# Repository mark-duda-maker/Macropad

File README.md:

## The Case

## The PCB

## The Schematic

## The Bom
4x M3x16mm screws
4x M3x5mx4mm heatset inserts
9x Blank DSA keycaps
9x MX-Style switches
9x Through-hole 1N4148 Diodes
1x 0.91" 128x32 OLED Display
1x EC11 Rotary Encoder
1x XIAO RP2040

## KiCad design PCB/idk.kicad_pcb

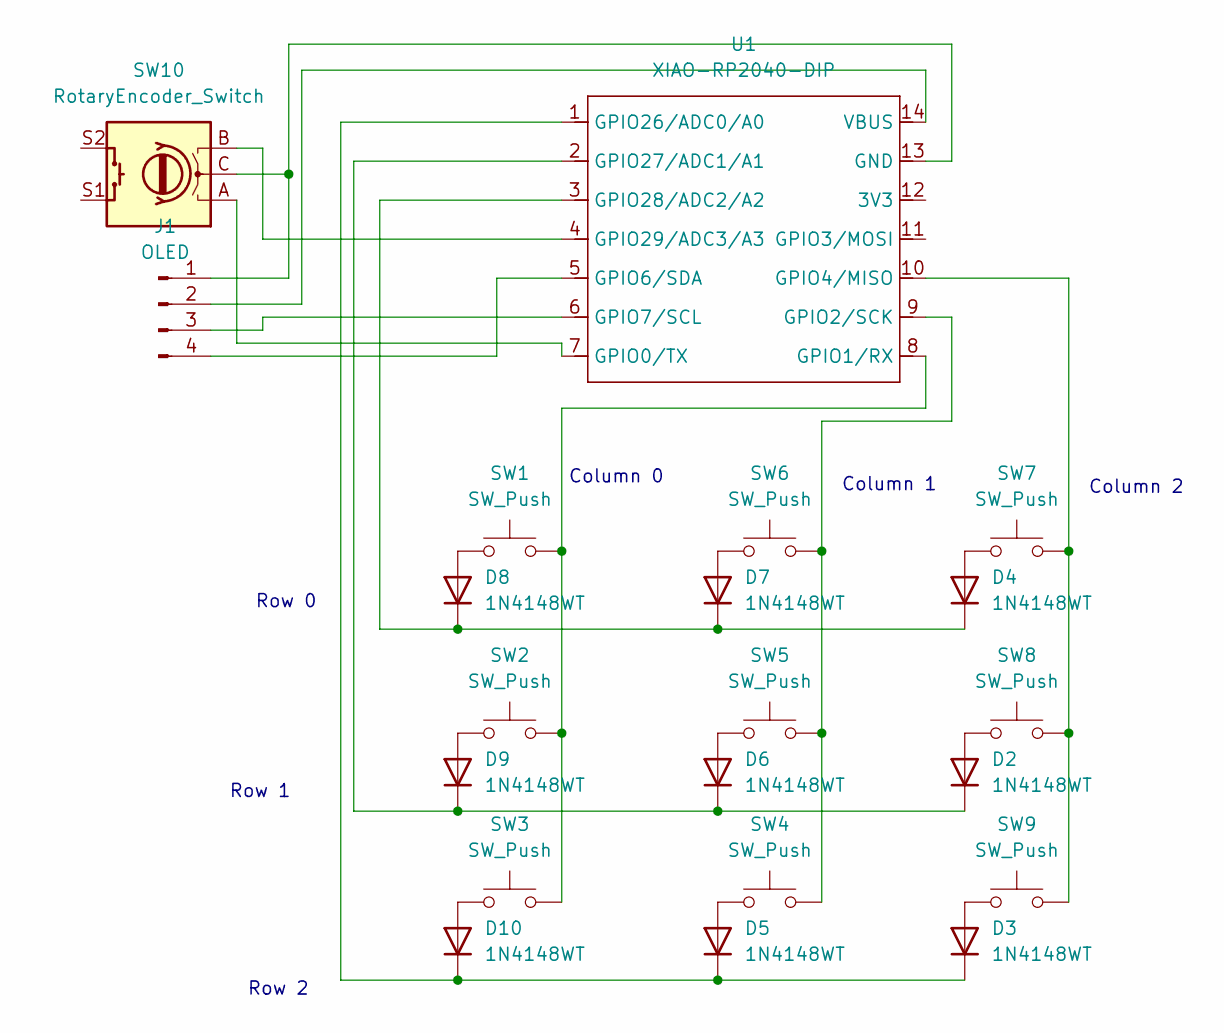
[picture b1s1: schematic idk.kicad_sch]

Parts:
D2, D3, D4, D5, D6, D7, D8, D9, D10: 1N4148WT; D_DO-35_SOD27_P7.62mm_Horizontal
J1: OLED; SSD1306-0.91-OLED-4pin-128x32
SW1, SW2, SW3, SW4, SW5, SW6, SW7, SW8, SW9: SW_Push; SW_Cherry_MX_1.00u_PCB
SW10: RotaryEncoder_Switch; RotaryEncoder_Alps_EC11E-Switch_Vertical_H20mm_CircularMoun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
U1: XIAO-RP2040-DIP

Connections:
unnamed: D2.2 (A), SW8.1
unnamed: D2.1 (K), D6.1 (K), D9.1 (K), U1.2 (GPIO27/ADC1/A1)
unnamed: D3.2 (A), SW9.1
unnamed: D4.2 (A), SW7.1
unnamed: D4.1 (K), D7.1 (K), D8.1 (K), U1.3 (GPIO28/ADC2/A2)
unnamed: D5.2 (A), SW4.1
unnamed: D6.2 (A), SW5.1
unnamed: D7.2 (A), SW6.1
unnamed: D8.2 (A), SW1.1
unnamed: D9.2 (A), SW2.1
unnamed: D10.2 (A), SW3.1
unnamed: D3.1 (K), D5.1 (K), D10.1 (K), U1.1 (GPIO26/ADC0/A0)
unnamed: J1.1, SW10.C, U1.13 (GND)
unnamed: J1.2, U1.14 (VBUS)
unnamed: J1.3, U1.6 (GPIO7/SCL)
unnamed: J1.4, U1.5 (GPIO6/SDA)
unnamed: SW10.A, U1.7 (GPIO0/TX)
unnamed: SW1.2, SW2.2, SW3.2, U1.8 (GPIO1/RX)
unnamed: SW4.2, SW5.2, SW6.2, U1.9 (GPIO2/SCK)
unnamed: SW7.2, SW8.2, SW9.2, U1.10 (GPIO4/MISO)
unnamed: SW10.B, U1.4 (GPIO29/ADC3/A3)

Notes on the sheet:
Row 1
Column 2
Column 1
Column 0
Row 2
Row 0

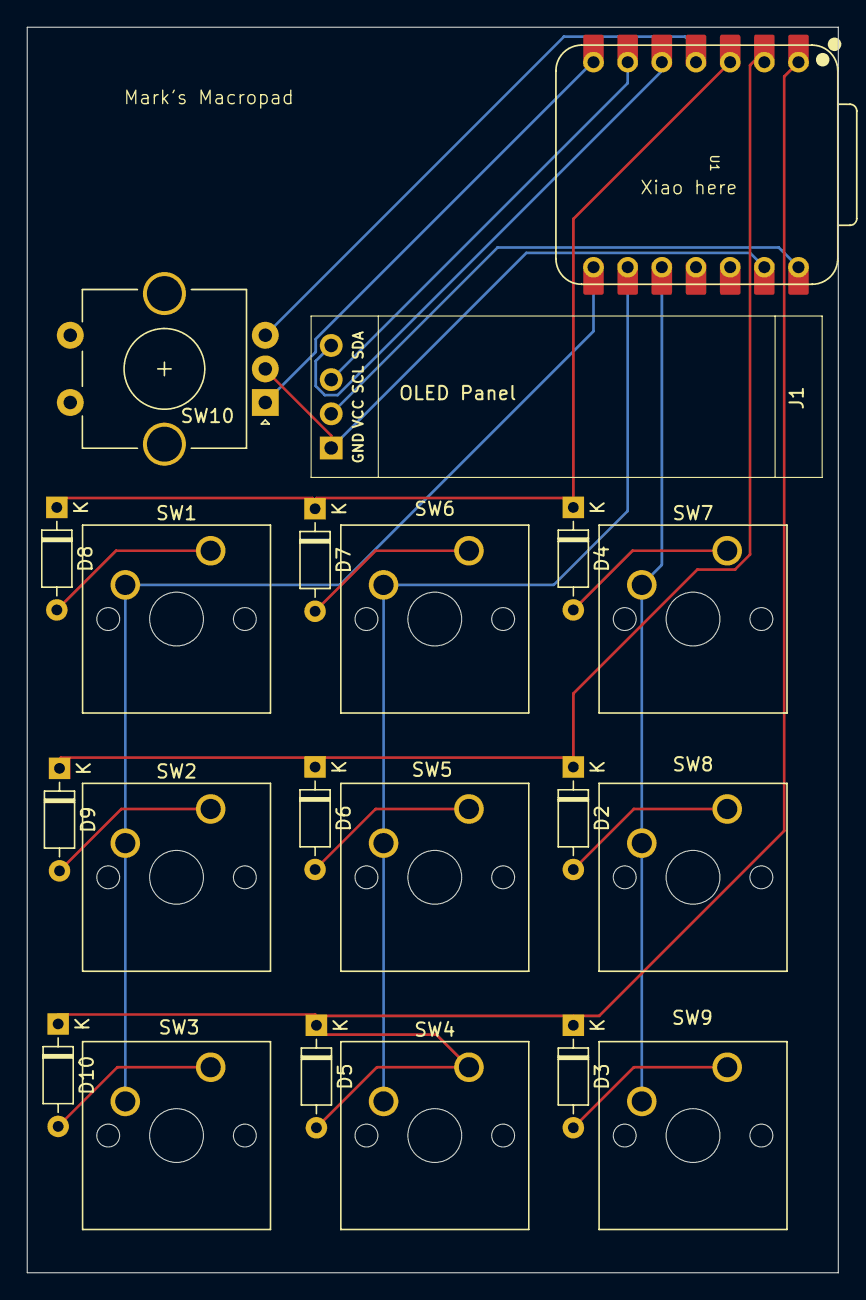
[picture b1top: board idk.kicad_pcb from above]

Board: 2 copper layers, 60.3 x 92.6 mm, 21 parts (0 on the bottom side), 21 nets.

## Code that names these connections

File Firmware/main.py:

import board
from kmk.kmk_keyboard import KMKKeyboard
from kmk.keys import KC
from kmk.scanners import DiodeOrientation
from kmk.modules.layers import Layers
from kmk.modules.encoder import EncoderHandler
from kmk.extensions.peg_oled_Display import Oled, OledDisplayMode, OledReactionType, OledData
from kmk.extensions.media_keys import MediaKeys

# Initialize keyboard
keyboard = KMKKeyboard()

# Initialize modules
layers = Layers()
encoder_handler = EncoderHandler()
media_keys = MediaKeys()

# Add modules to keyboard
keyboard.modules = [layers, encoder_handler]
keyboard.extensions = [media_keys]

# Define matrix pins - ACTUAL WIRING
# Rows: Pin 1 (GPIO26/A0), Pin 2 (GPIO27/A1), Pin 3 (GPIO28/A2)
# Columns: Pin 8 (GPIO1/RX), Pin 9 (GPIO2/SCK), Pin 10 (GPIO4/MISO)
keyboard.col_pins = (board.D1, board.D2, board.D4)  # Column 0, Column 1, Column 2
keyboard.row_pins = (board.D26, board.D27, board.D28)  # Row 0, Row 1, Row 2
keyboard.diode_orientation = DiodeOrientation.COL2ROW

# Configure rotary encoder - ACTUAL WIRING
# A -> Pin 7 (GPIO0/TX), B -> Pin 4 (GPIO29/A3)
# Format: (pin_a, pin_b, button_pin, divisor)
encoder_handler.pins = ((board.D0, board.D29, None, False),)

# Configure OLED Display
# SDA -> GPIO6, SCL -> GPIO7
oled_ext = Oled(
    OledData(
        corner_one={0: OledReactionType.STATIC, 1: ["Layer"]},
        corner_two={
            0: OledReactionType.LAYER,
            1: ["Productivity", "Gaming", "Media", "Soundboard"]
        },
    ),
    toDisplay=OledDisplayMode.TXT,
    flip=False,
)
keyboard.extensions.append(oled_ext)

# Define custom macros for each mode
# Productivity macros
COPY = KC.LCTRL(KC.C)
PASTE = KC.LCTRL(KC.V)
CUT = KC.LCTRL(KC.X)
UNDO = KC.LCTRL(KC.Z)
SAVE = KC.LCTRL(KC.S)
SELECT_ALL = KC.LCTRL(KC.A)
FIND = KC.LCTRL(KC.F)
NEW_TAB = KC.LCTRL(KC.T)
CLOSE_TAB = KC.LCTRL(KC.W)

# Gaming macros
QUICK_SAVE = KC.F5
QUICK_LOAD = KC.F9
SCREENSHOT = KC.F12
INVENTORY = KC.TAB
MAP = KC.M
JUMP = KC.SPACE
CROUCH = KC.LCTRL
RELOAD = KC.R
INTERACT = KC.E

# Media macros
PLAY_PAUSE = KC.MEDIA_PLAY_PAUSE
NEXT_TRACK = KC.MEDIA_NEXT_TRACK
PREV_TRACK = KC.MEDIA_PREV_TRACK
VOL_DOWN = KC.MEDIA_VOLUME_DOWN
MUTE = KC.MEDIA_MUTE
VOL_UP = KC.MEDIA_VOLUME_UP
STOP = KC.MEDIA_STOP
CALC = KC.MACRO("calc")  # Opens calculator on Windows
BROWSER = KC.MACRO("Chrome")  # Opens Chrome
#those last 2 probably don't work but I am going to fix that once I can test the other stuff

# Discord Soundboard macros
# These trigger Discord's default soundboard keybinds (F13-F21)
# You'll need to assign these keys to your soundboard sounds in Discord settings
SOUND1 = KC.F13  
SOUND2 = KC.F14  
SOUND3 = KC.F15  
SOUND4 = KC.F16 
SOUND5 = KC.F17  
SOUND6 = KC.F18 
SOUND7 = KC.F19  
SOUND8 = KC.F20  
SOUND9 = KC.F21  

# Define keymap with 4 layers
# Each layer has 9 keys arranged in 3x3 matrix
keyboard.keymap = [
    # Layer 0: Productivity Mode
    [
        COPY,       PASTE,      CUT,        # Row 1: SW1, SW2, SW7
        UNDO,       SAVE,       SELECT_ALL, # Row 2: SW5, SW3, SW8
        FIND,       NEW_TAB,    CLOSE_TAB,  # Row 3: SW6, SW4, SW9
    ],
    # Layer 1: Gaming Mode
    [
        QUICK_SAVE, QUICK_LOAD, SCREENSHOT, # Row 1
        INVENTORY,  MAP,        JUMP,       # Row 2
        CROUCH,     RELOAD,     INTERACT,   # Row 3
    ],
    # Layer 2: Media Mode
    [
        PLAY_PAUSE, NEXT_TRACK, PREV_TRACK, # Row 1
        VOL_DOWN,   MUTE,       VOL_UP,     # Row 2
        STOP,       CALC,       BROWSER,    # Row 3
    ],
    # Layer 3: Discord Soundboard Mode
    [
        SOUND1,     SOUND2,     SOUND3,     # Row 1
        SOUND4,     SOUND5,     SOUND6,     # Row 2
        SOUND7,     SOUND8,     SOUND9,     # Row 3
    ],
]

# Configure encoder behavior per layer
# (Turn Left, Turn Right, Button Press)
encoder_handler.map = [
    # Layer 0: Productivity
    ((KC.TO(3), KC.TO(1), KC.NO),),  # Left->Layer 3, Right->Layer 1
    # Layer 1: Gaming
    ((KC.TO(0), KC.TO(2), KC.NO),),  # Left->Layer 0, Right->Layer 2
    # Layer 2: Media
    ((KC.TO(1), KC.TO(3), KC.NO),),  # Left->Layer 1, Right->Layer 3
    # Layer 3: Soundboard
    ((KC.TO(2), KC.TO(0), KC.NO),),  # Left->Layer 2, Right->Layer 0
]

if __name__ == '__main__':
    keyboard.go()

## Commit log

2025-12-03 The thing
2025-12-03 tweaks
2025-12-03 more tweaks
2025-12-03 even more tweaks
2025-12-03 I think i typed it write this time
2025-12-03 please be right
2025-12-03 I hate that i need to write this for to fix a small typo
2025-12-03 Slight case tweaks
